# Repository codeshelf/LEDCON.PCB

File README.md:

LEDCON.PCB
==========

LED Controller PCB design files (no production files)

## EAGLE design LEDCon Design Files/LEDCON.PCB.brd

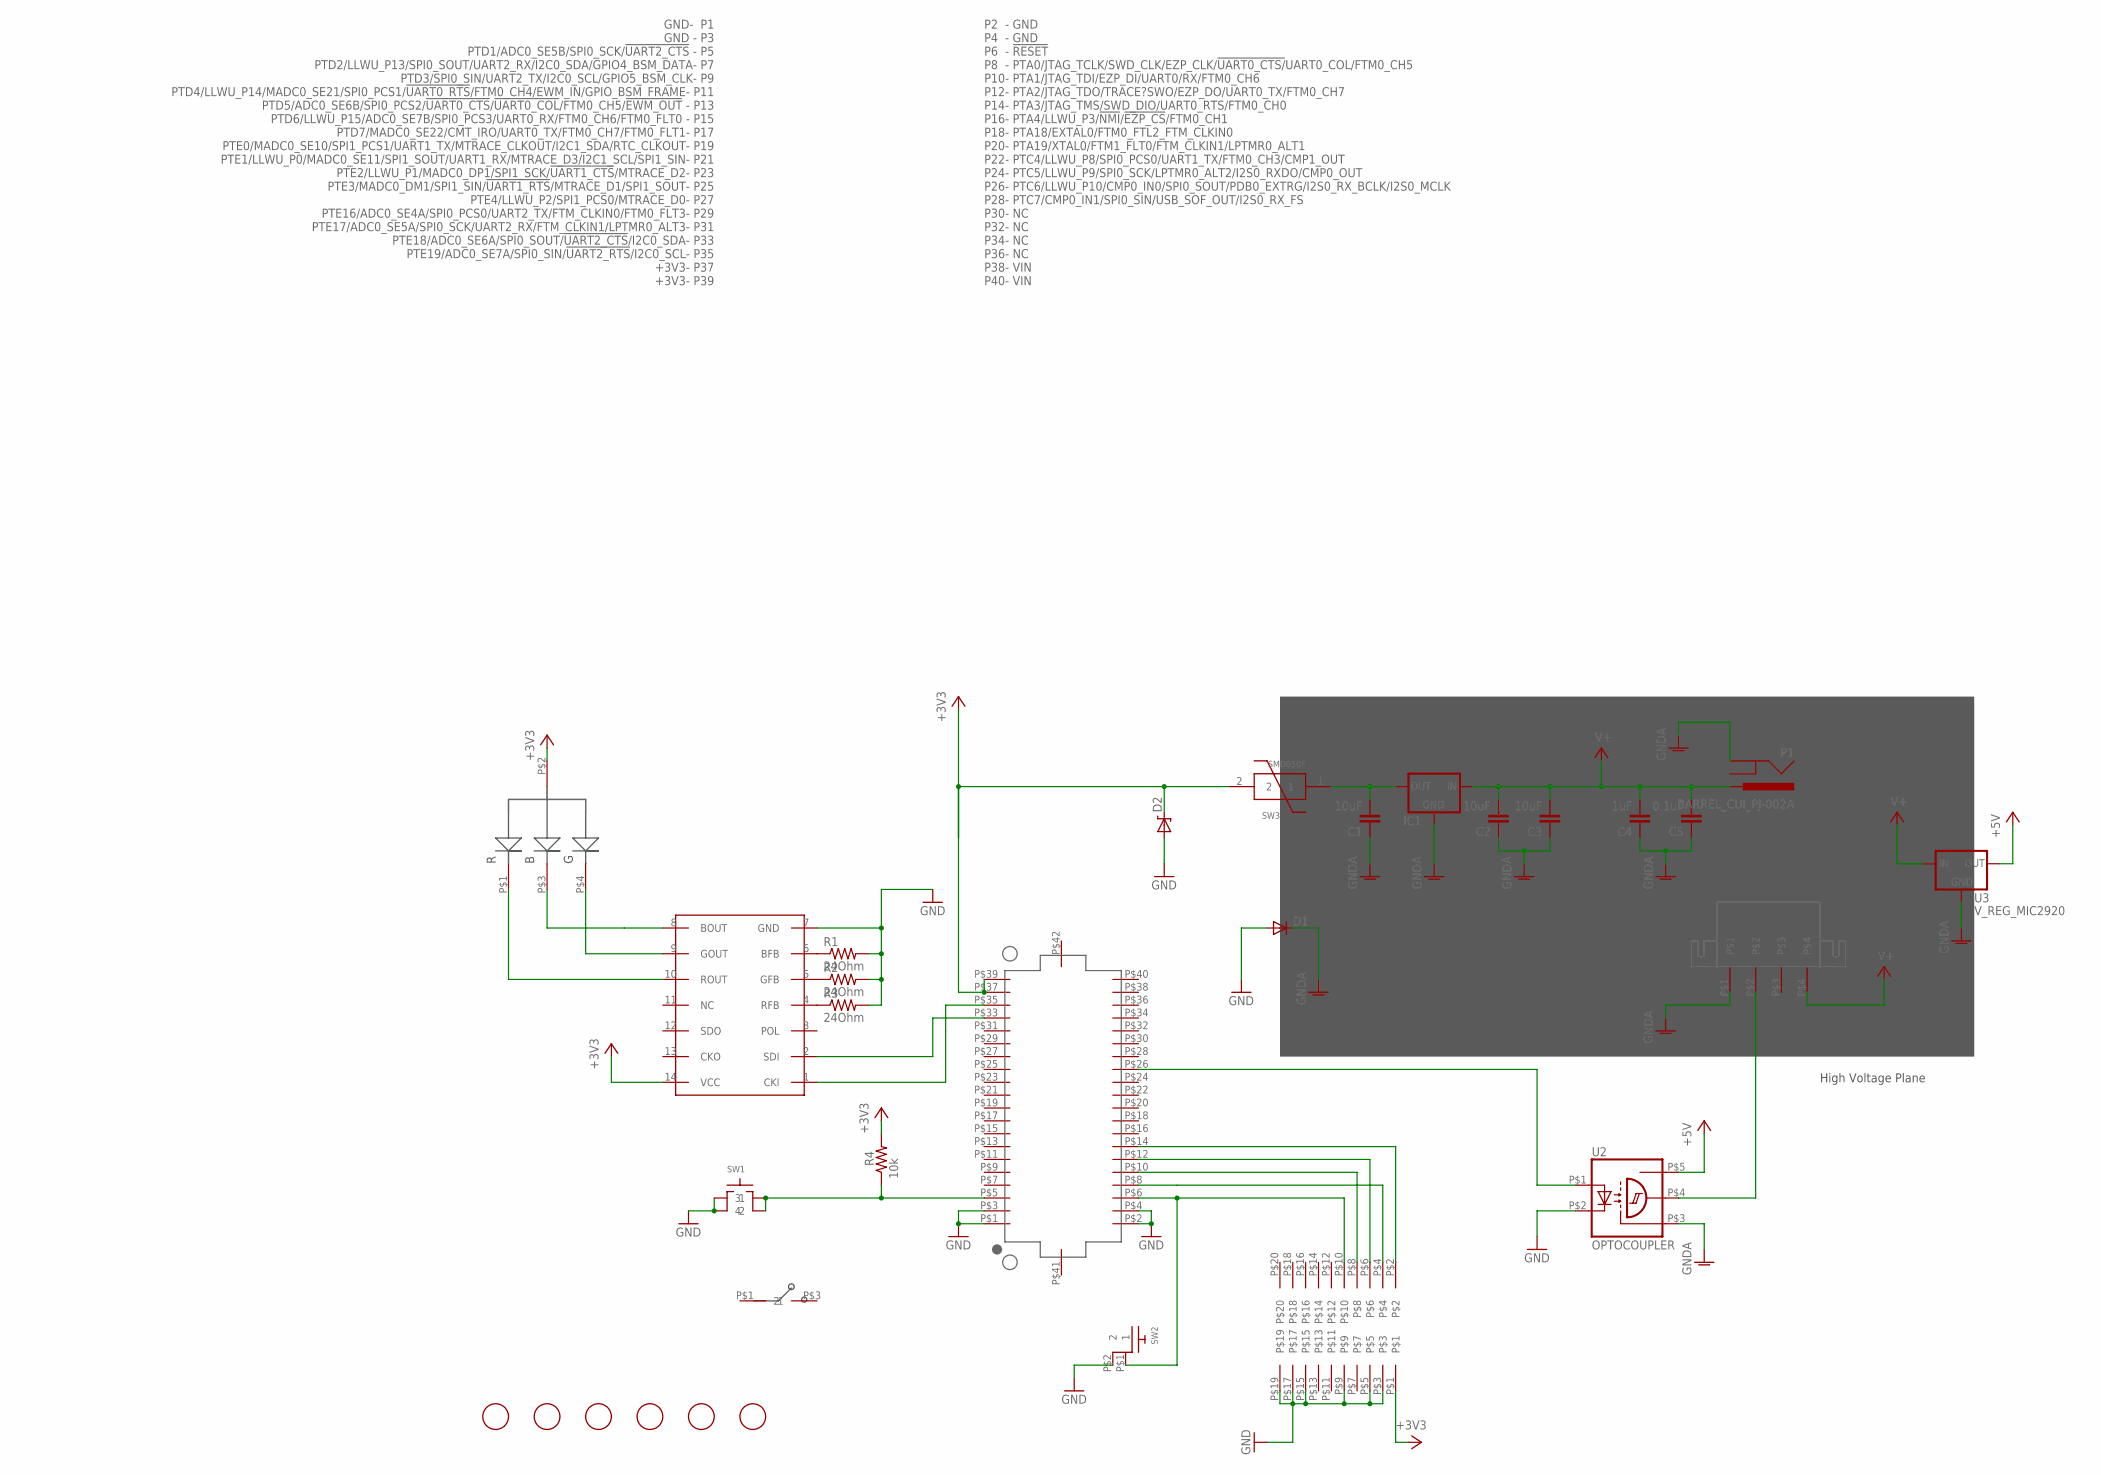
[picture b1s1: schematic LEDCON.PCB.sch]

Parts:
AWESOME: CJS
C1: 10uF; C0805
C2, C3: 10uF; C1210K
C4: 1uF; C0805
C5: 0.1uF; C0805
D1: DIODESMA; SMA-DIODE
D2: DIODE-ZENERSMB; SMB-DIODE
IC1: V_REG_78XX; TO220-TRACO
J1: MATE-N-LOK_643230-1
JTAG: 2X10JTAGSMD; 2X10JTAG-SMD
KW2: DF12_F
LED1: RGLBED; RGBLED
P1: BARREL_CUI_PJ-002A
R1, R2, R3: 24Ohm; RF-C0805
R4: 10k; RF-C0805
SW1: SWITCH-TACTILE; ESWITCH-TL3301PF
SW2: RA_BUTTON
SW3: SMD050F; C1210
U1: WS2801; SO14
U2: OPTOCOUPLER; S06-5
U3: V_REG_MIC2920; SOT223
U$14, U$18, U$25, U$26, U$27, U$28: FIDUCIAL; FIDUCIAL_1MM

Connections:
+3V3: D2.C, JTAG.P$1, KW2.P$37 (+3V3), KW2.P$39 (+3V3), LED1.P$2 (ANODE), R4.2, SW3.2, U1.14 (VCC)
+5V: U2.P$5 (VCC), U3.3 (OUT)
DAT_5V: KW2.P$26 (PTC6/LLWU_P10/CMP0_IN0/SPI0_SOUT/PDB0_E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), U2.P$1 (A)
GND: D1.A, D2.A, JTAG.P$3, JTAG.P$5, JTAG.P$9, JTAG.P$15, JTAG.P$17, JTAG.P$19, KW2.P$1 (GND), KW2.P$2 (GND), KW2.P$3 (GND), KW2.P$4 (GND), R1.2, R2.2, R3.2, SW1.1, SW1.2, SW2.P$2 (2), U1.7 (GND), U2.P$2 (C)
GNDA: C1.1, C2.1, C3.1, C4.1, C5.1, D1.C, IC1.GND, J1.P$1, P1.P$2 (GND), U2.P$3 (GND), U3.2 (GND)
unnamed: C1.2, IC1.OUT, SW3.1
unnamed: J1.P$2, U2.P$4 (OUT)
unnamed: LED1.P$4 (GREEN), U1.9 (GOUT)
unnamed: LED1.P$3 (BLUE), U1.8 (BOUT)
unnamed: JTAG.P$2, KW2.P$14 (PTA3/JTAG_TMS/SWD_DIO/UART0_RTS/FTM0_CH0)
unnamed: LED1.P$1 (RED), U1.10 (ROUT)
unnamed: JTAG.P$6, KW2.P$12 (PTA2/JTAG_TDO/TRACE?SWO/EZP_DO/UART0_TX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)
unnamed: KW2.P$33 (PTE18/ADC0_SE6A/SPI0_SOUT/!UART2_CTS!/I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), U1.2 (SDI)
unnamed: R1.1, U1.6 (BFB)
unnamed: R2.1, U1.5 (GFB)
unnamed: R3.1, U1.4 (RFB)
unnamed: KW2.P$35 (PTE19/ADC0_SE7A/SPI0_SIN/!UART2_RTS!/I2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), U1.1 (CKI)
unnamed: JTAG.P$4, KW2.P$8 (PTA0/JTAG_TCLK/SWD_CLK/EZP_CLK/!UART0_C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)
unnamed: JTAG.P$8, KW2.P$10 (PTA1/JTAG_TDI/EZP_DI/UART0/RX/FTM0_CH6)
unnamed: KW2.P$5 (PTD1/ADC0_SE5B/SPI0_SCK/!UART2_CTS), R4.1, SW1.3, SW1.4
SW2: JTAG.P$10, KW2.P$6 (!RESET), SW2.P$1 (1)
V+: C2.2, C3.2, C4.2, C5.2, IC1.IN, J1.P$4, P1.P$1 (PWR), U3.1 (IN)

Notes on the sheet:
High Voltage Plane

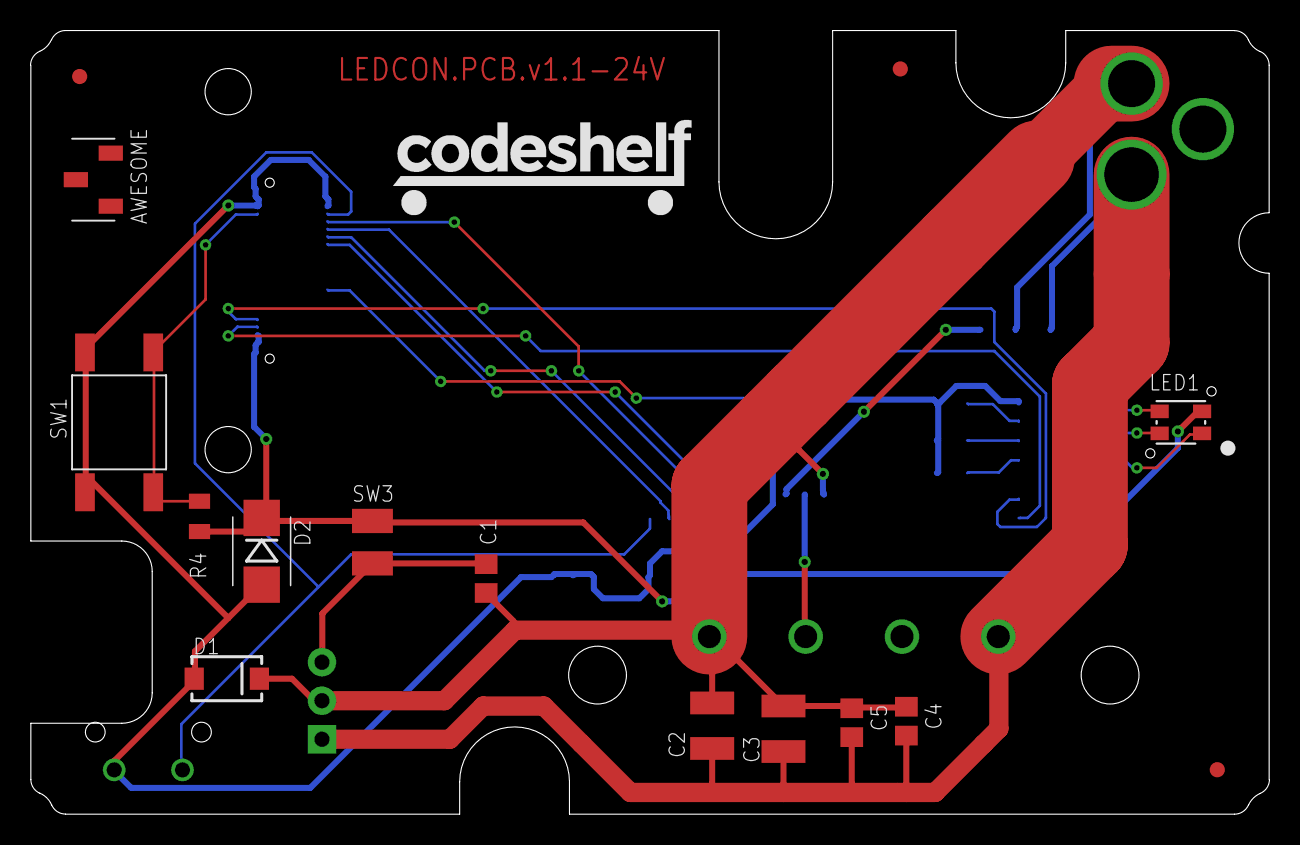
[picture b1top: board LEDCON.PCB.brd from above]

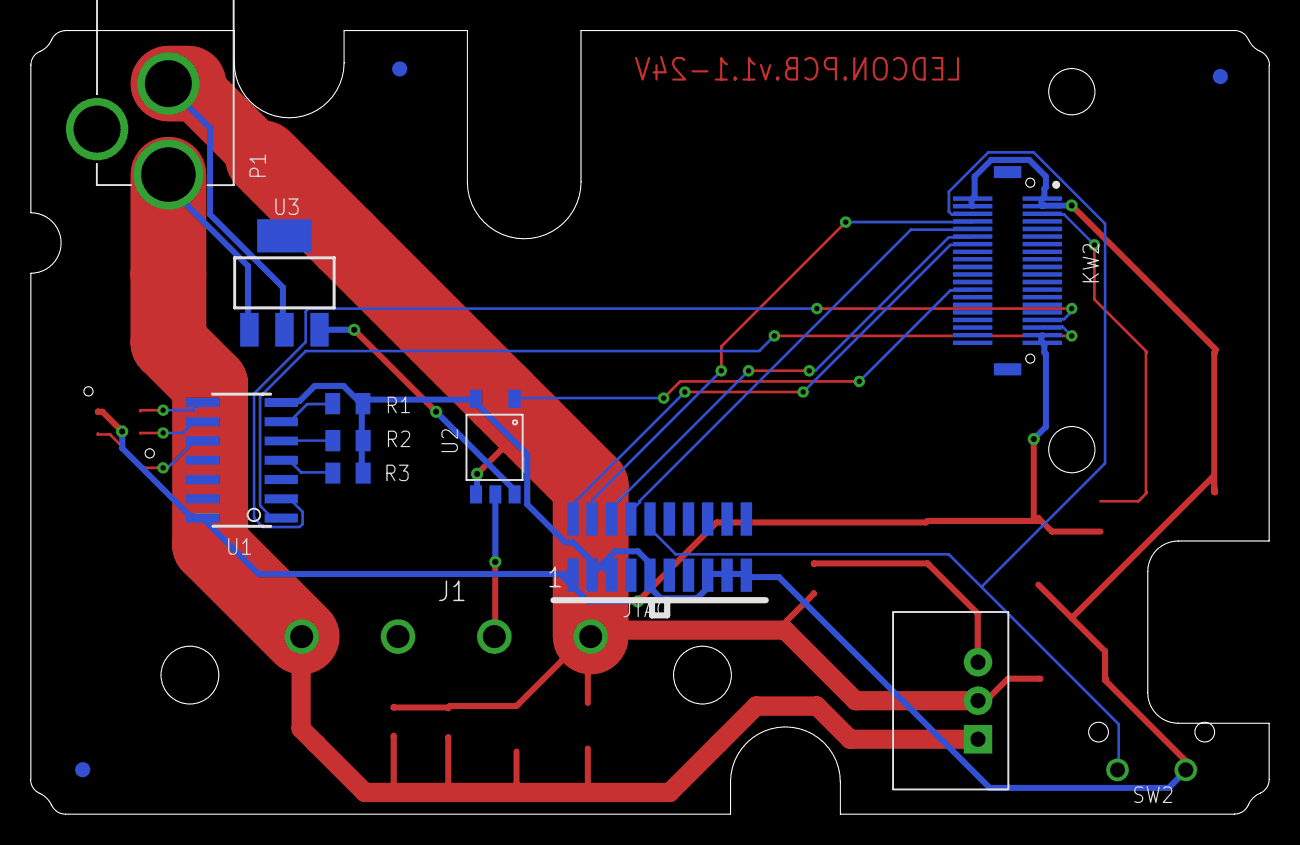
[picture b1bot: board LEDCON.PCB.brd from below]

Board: 2 copper layers, 81.7 x 51.7 mm, 30 parts (15 on the bottom side), 22 nets.

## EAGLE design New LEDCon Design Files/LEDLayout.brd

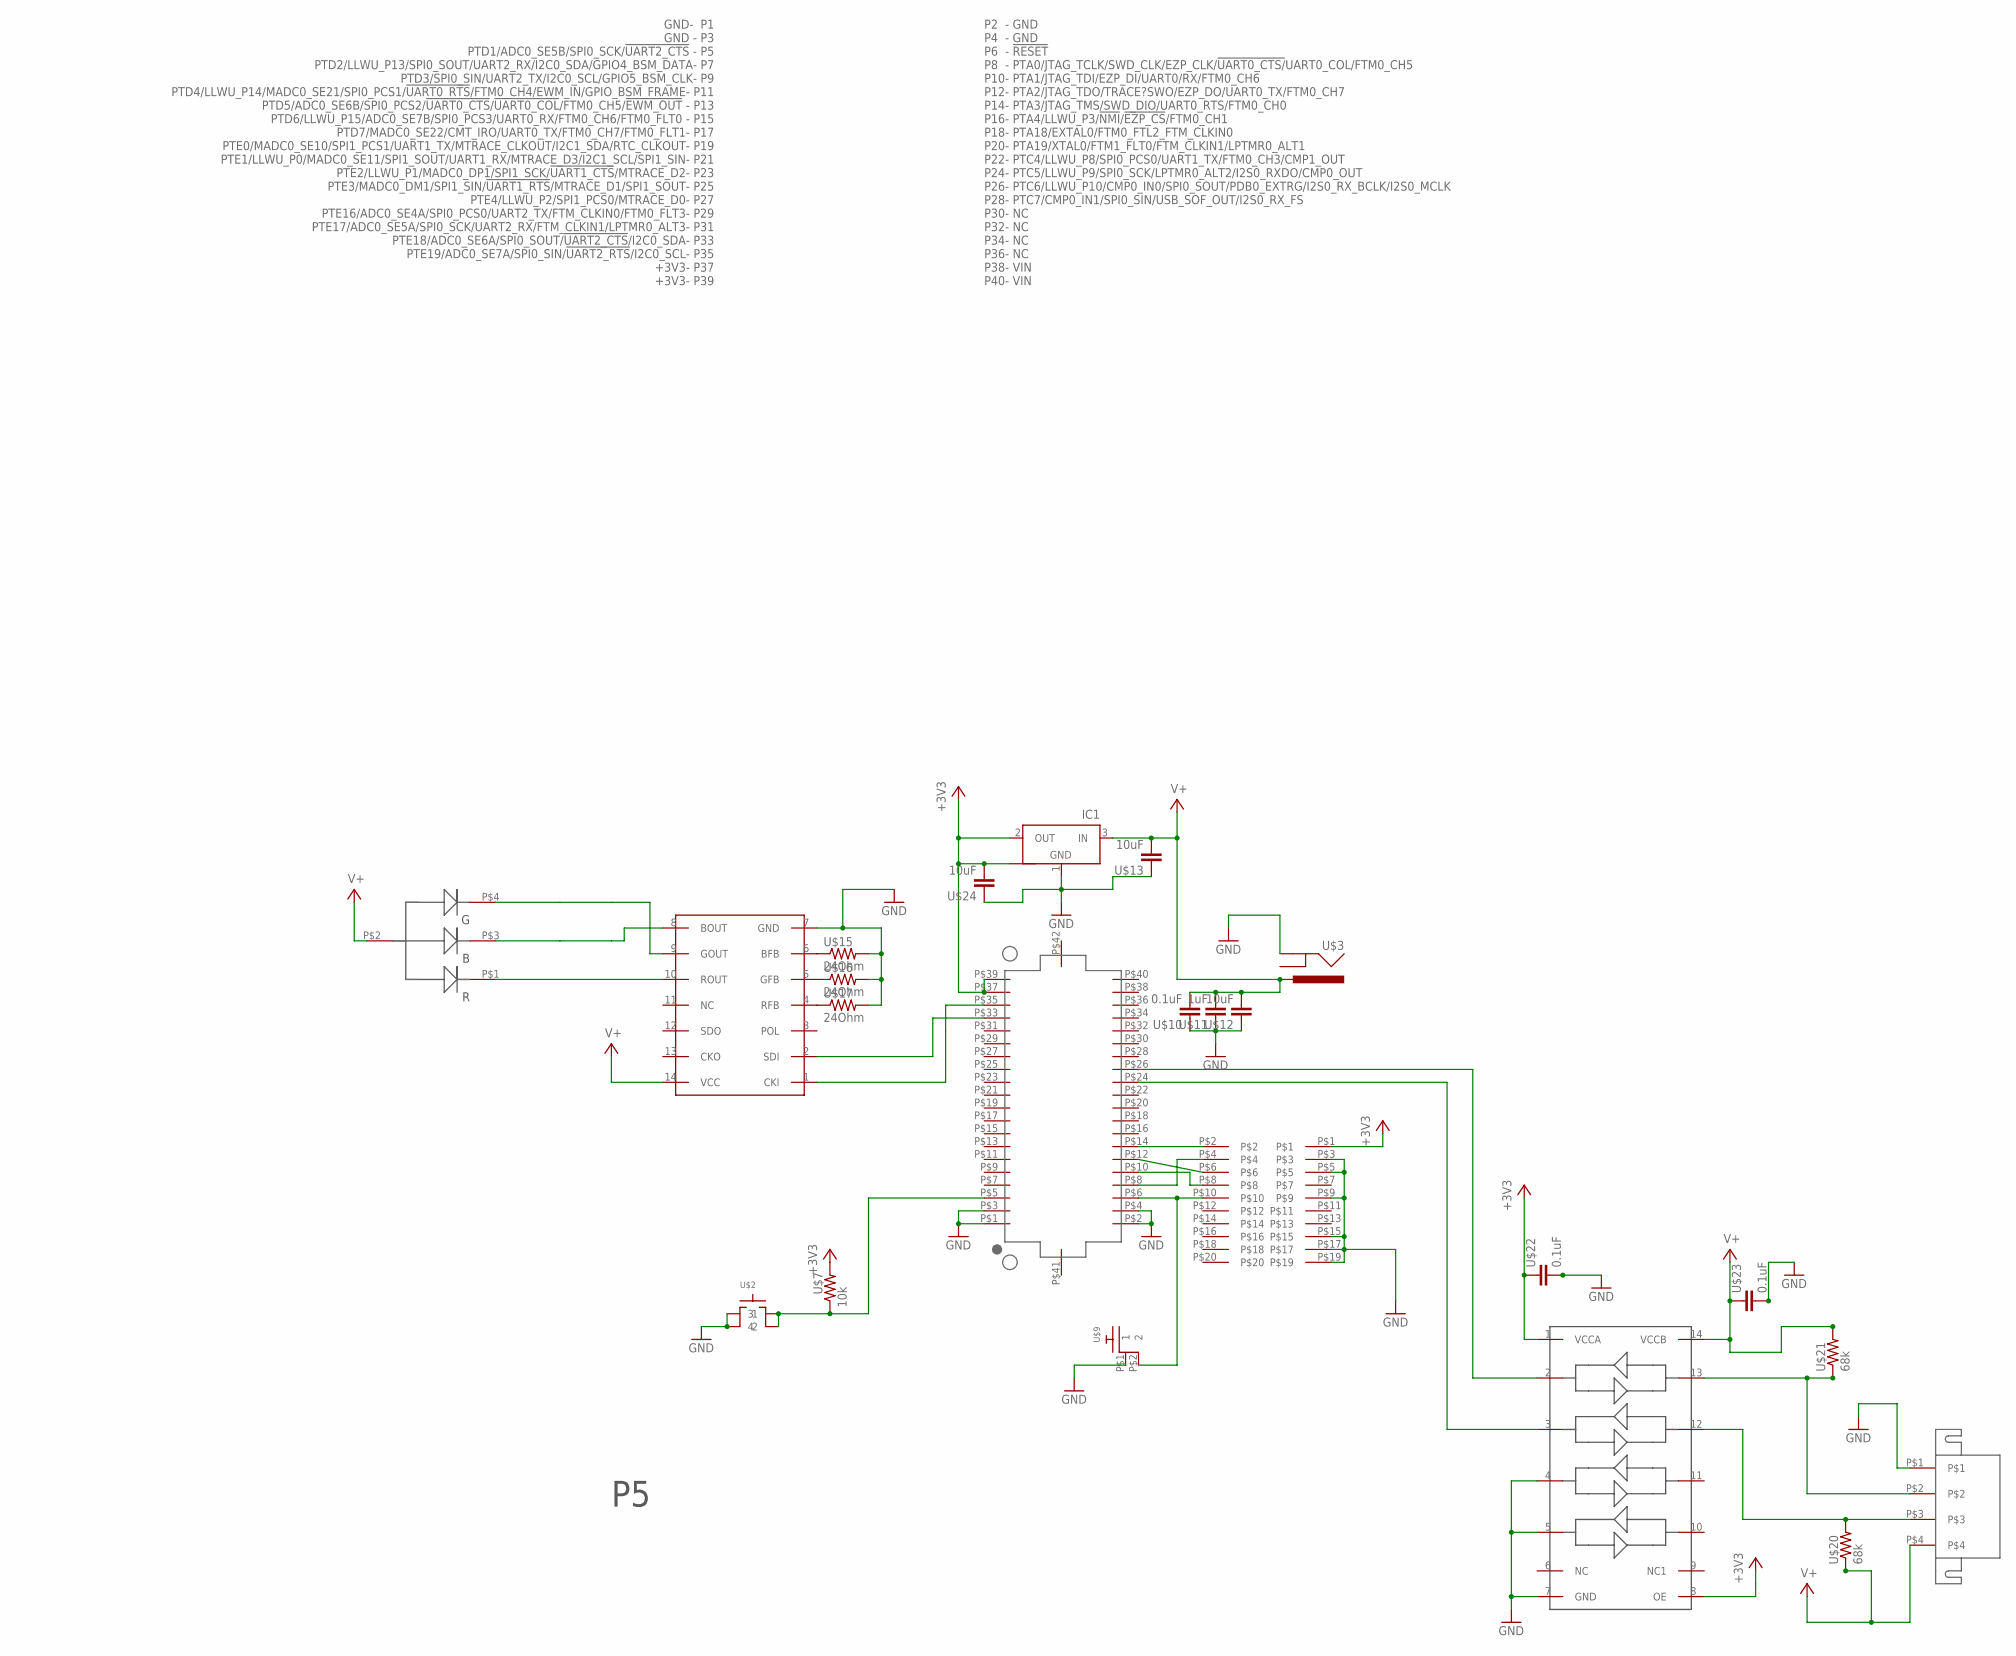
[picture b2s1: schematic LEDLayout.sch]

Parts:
IC1: NCP1117ST33T3G_1; SOT223
U$1: MATE-N-LOK_643230-1
U$2: SWITCH-TACTILE; ESWITCH-TL3301PF
U$3: BARREL_CUI_PJ-002A
U$4: DF12_F
U$5: RGLBED; RGBLED
U$6: TXB0104; PW_R-PDSO-G14
U$7: 10k; RF-C0805
U$8: WS2801; SO14
U$9: RA_BUTTON
U$10, U$22, U$23: 0.1uF; C0805
U$11: 1uF; C0805
U$12, U$13, U$24: 10uF; C0805
U$15, U$16, U$17: 24Ohm; RF-C0805
U$19: 2X10JTAG
U$20, U$21: 68k; RF-C0805

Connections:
+3V3: IC1.2 (OUT), IC1.4 (OUT1), U$4.P$37 (+3V3), U$4.P$39 (+3V3), U$6.1 (VCCA), U$6.8 (OE), U$7.2, U$19.P$1, U$22.1, U$24.2
CLK_5V: U$1.P$3, U$6.12, U$20.2
DAT_5V: U$1.P$2, U$6.13, U$21.1
GND: IC1.1 (GND), U$1.P$1, U$2.1, U$2.2, U$3.P$2 (GND), U$4.P$1 (GND), U$4.P$2 (GND), U$4.P$3 (GND), U$4.P$4 (GND), U$6.4, U$6.5, U$6.7 (GND), U$8.7 (GND), U$9.P$1 (1), U$10.1, U$11.1, U$12.1, U$13.1, U$15.2, U$16.2, U$17.2, U$19.P$3, U$19.P$5, U$19.P$9, U$19.P$15, U$19.P$17, U$19.P$19, U$22.2, U$23.2, U$24.1
unnamed: U$4.P$26 (PTC6/LLWU_P10/CMP0_IN0/SPI0_SOUT/PDB0_E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), U$6.2
unnamed: U$4.P$24 (PTC5/LLWU_P8/SPI0_PCS0/UART1_TX/FTM0_CH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), U$6.3
unnamed: U$4.P$6 (!RESET), U$9.P$2 (2), U$19.P$10
unnamed: U$5.P$4 (GREEN), U$8.9 (GOUT)
unnamed: U$5.P$3 (BLUE), U$8.8 (BOUT)
unnamed: U$4.P$14 (PTA3/JTAG_TMS/SWD_DIO/UART0_RTS/FTM0_CH0), U$19.P$2
unnamed: U$5.P$1 (RED), U$8.10 (ROUT)
unnamed: U$4.P$12 (PTA2/JTAG_TDO/TRACE?SWO/EZP_DO/UART0_TX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), U$19.P$6
unnamed: U$4.P$33 (PTE18/ADC0_SE6A/SPI0_SOUT/!UART2_CTS!/I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), U$8.2 (SDI)
unnamed: U$8.6 (BFB), U$15.1
unnamed: U$8.5 (GFB), U$16.1
unnamed: U$8.4 (RFB), U$17.1
unnamed: U$4.P$35 (PTE19/ADC0_SE7A/SPI0_SIN/!UART2_RTS!/I2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), U$8.1 (CKI)
unnamed: U$4.P$8 (PTA0/JTAG_TCLK/SWD_CLK/EZP_CLK/!UART0_C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), U$19.P$4
unnamed: U$4.P$10 (PTA1/JTAG_TDI/EZP_DI/UART0/RX/FTM0_CH6), U$19.P$8
unnamed: U$2.3, U$2.4, U$4.P$5 (PTD1/ADC0_SE5B/SPI0_SCK/!UART2_CTS), U$7.1
V+: IC1.3 (IN), U$1.P$4, U$3.P$1 (PWR), U$5.P$2 (ANODE), U$6.14 (VCCB), U$8.14 (VCC), U$10.2, U$11.2, U$12.2, U$13.2, U$20.1, U$21.2, U$23.1

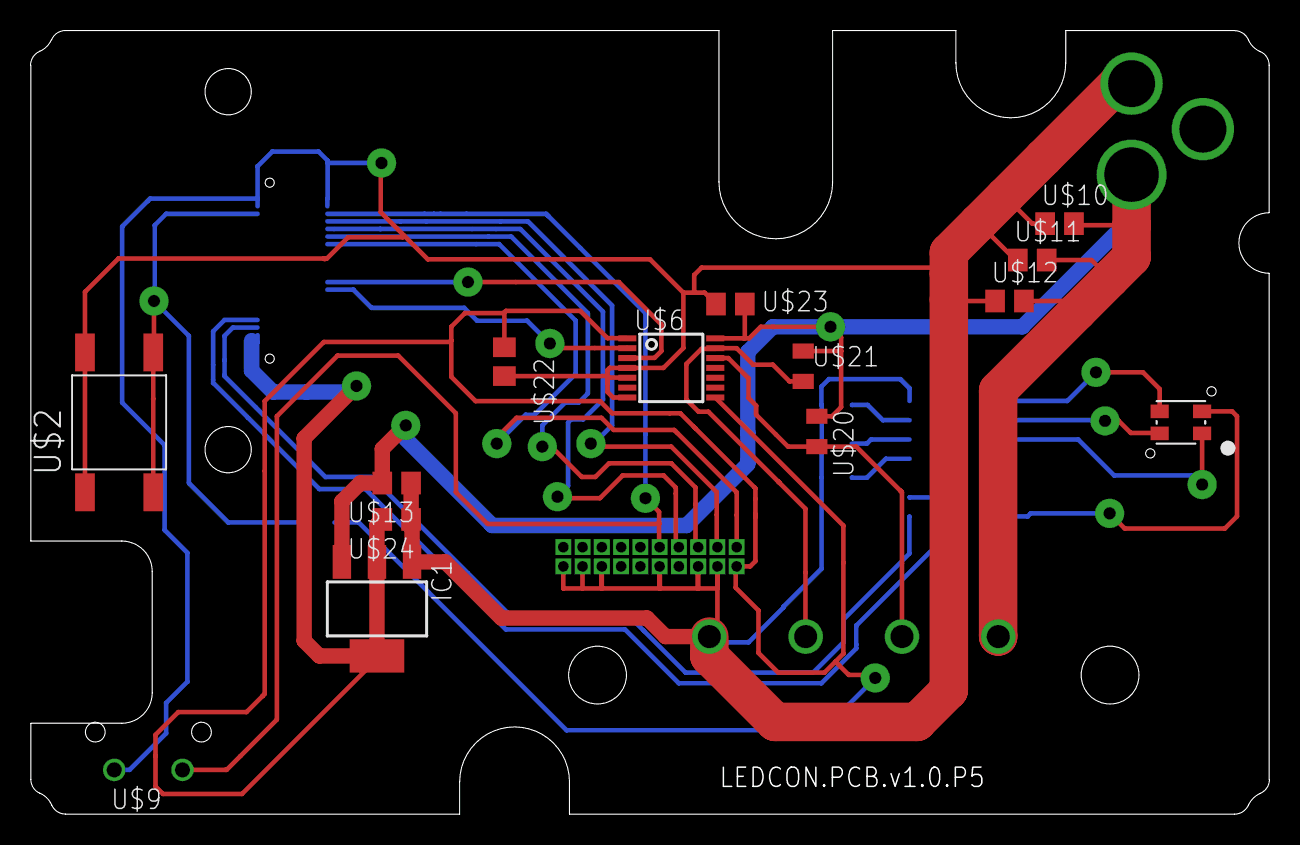
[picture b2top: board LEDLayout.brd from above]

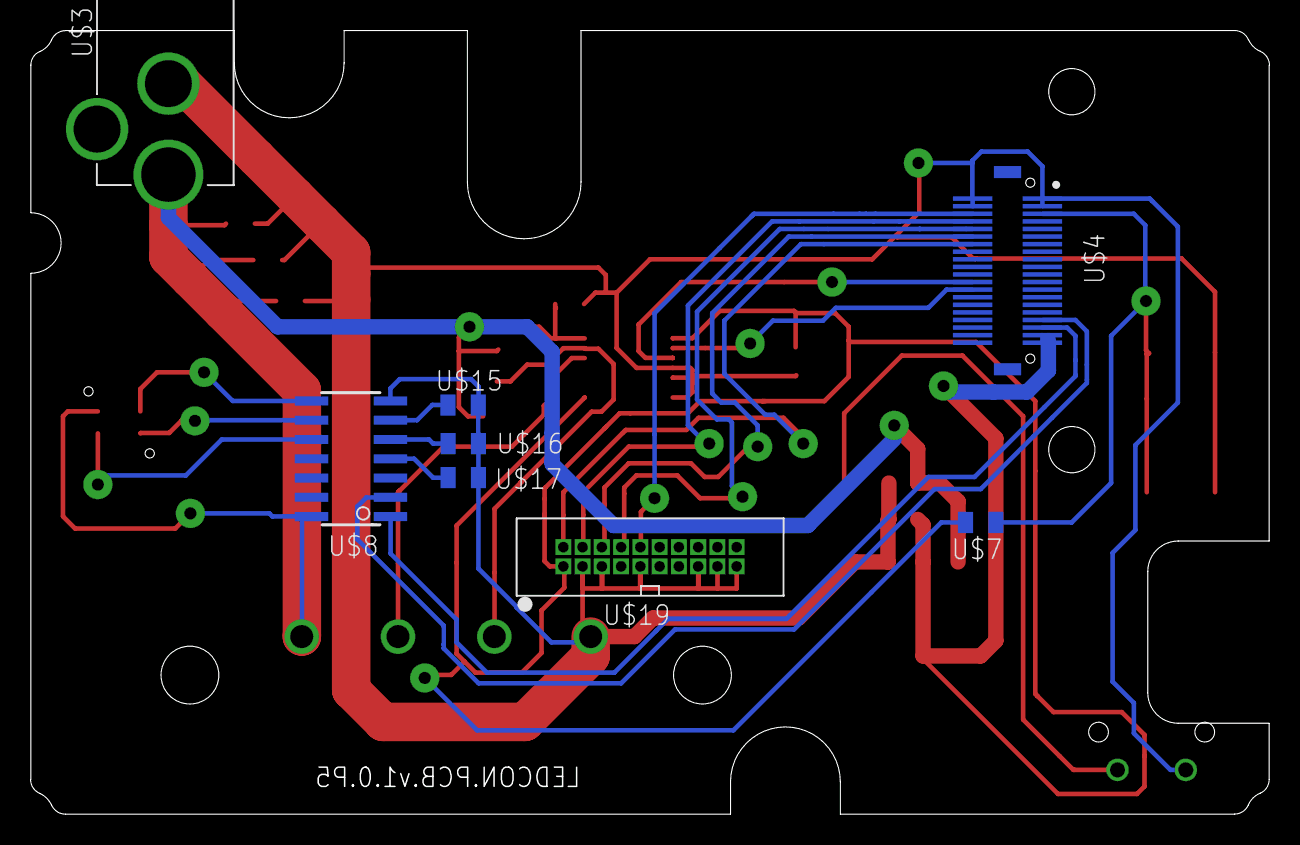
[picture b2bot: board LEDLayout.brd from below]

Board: 2 copper layers, 81.7 x 51.7 mm, 23 parts (9 on the bottom side), 21 nets.

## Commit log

2015-01-04 Finishing prototype routing
    Still need LED information.
2015-01-05 Finished routing 1st prototype
    Added WS2801, choice resistors & finished routing
2015-01-13 Added JTAG header, fixed data / clock switch
    Moved TXB0104 to front side
2015-01-15 Prototype 3
    Added filter caps and output data /clk pullups
2015-01-23 Prototype 4
    Fixed LED, removed jumpers, fixed JTAG traces and added RA reset button
2015-02-19 Prototype 5
    Added Vreg, caps, fixed LED, assigned values & PNs, removed 0402
    footprints. Pending exporting of production files
2015-02-20 LEDCON.PCB.v1.0 pre-release
    Pending checklist processing.
    Fixed reset switch orientation, added planes, silk screen labelling,
    added all part numbers, exported production files, added BOM, ECO and
    FAB notes.
2015-02-21 LEDCON.PCB.v1.0
    Everything done. Release version.
2015-10-20 Removed level shifter (no layout change)
    Also test commit for branch.
2015-11-19 24V V1
    LED still there (need to blast off). Added 24V reg + capacitors
2016-01-08 Ignore lock files for Eagle 7
2016-01-08 Ignore all lock files for Eagle 7
2016-01-08 sync repo
    sync work while rafael was out
2016-01-18 Two-plane isolation version 1
    All of the design changes needed to make a 2-plane isolation design.
2016-01-25 Redo the layout per the Codeshelf.standard DRU file
2016-03-11 Update BOM
2016-03-18 Add centroid files

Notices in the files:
parts and their libraries:
SparkFun: Licensing: CC v3.0 Share-Alike You are welcome to use this library for commercial purposes.
